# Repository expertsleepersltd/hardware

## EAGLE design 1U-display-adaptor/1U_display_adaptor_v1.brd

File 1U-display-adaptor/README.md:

1U Display Adaptor
=====

A mount for an OLED display to fit a Eurorack 1U row.

Copyright (c) 2022 Expert Sleepers Ltd

Please refer to [LICENSE.md](LICENSE.md) for licensing information.

Please note that Expert Sleepers® is a registered trade mark in the UK and the EU. Remove any branding before making a derivative work.

Board and schematic are in [EAGLE](https://en.wikipedia.org/wiki/EAGLE_(program)) format.

View as web page: https://expertsleepersltd.github.io/hardware/1U-display-adaptor/

The PCB can be purchased here: https://www.thonk.co.uk/shop/expert-sleepers-1u-display-pcb/

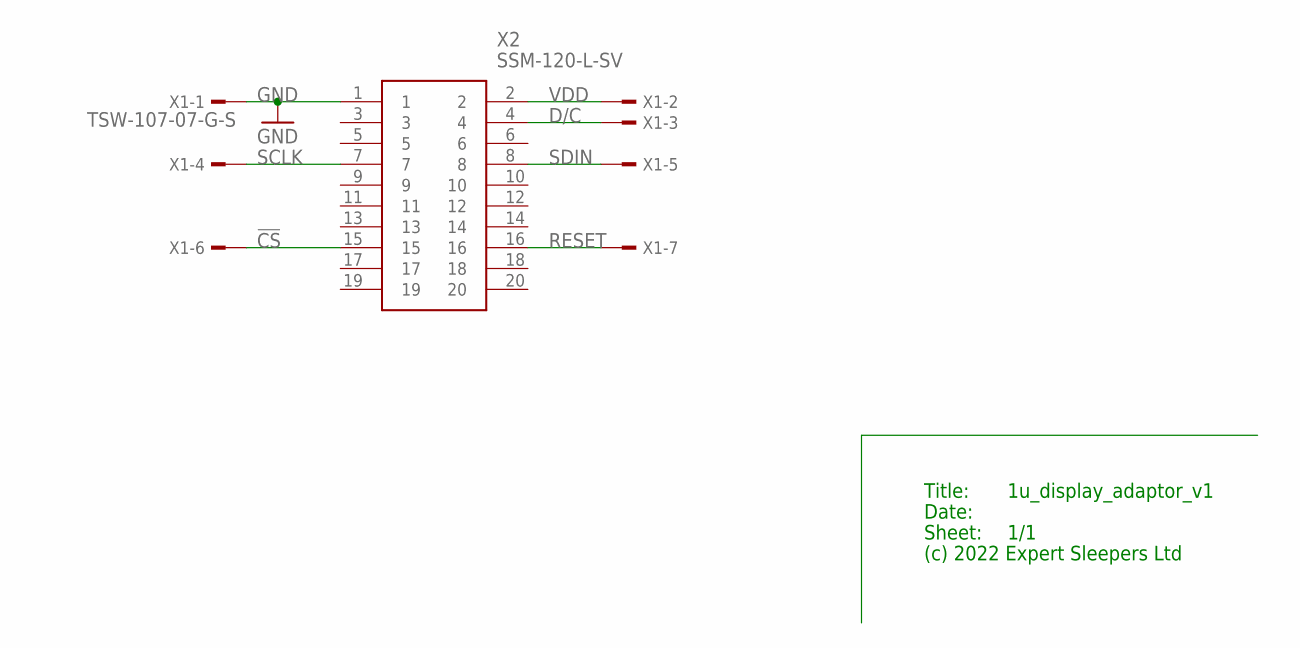
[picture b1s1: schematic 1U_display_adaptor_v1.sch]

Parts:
X1: TSW-107-07-G-S; TSW-107-XX-G-S
X2: SSM-120-L-SV; SSM120LSV

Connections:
!CS: X1.6, X2.15
D/C: X1.3, X2.4
GND: X1.1, X2.1
RESET: X1.7, X2.16
SCLK: X1.4, X2.7
SDIN: X1.5, X2.8
VDD: X1.2, X2.2

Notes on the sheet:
Title:
Date:
Sheet:
(c) 2022 Expert Sleepers Ltd

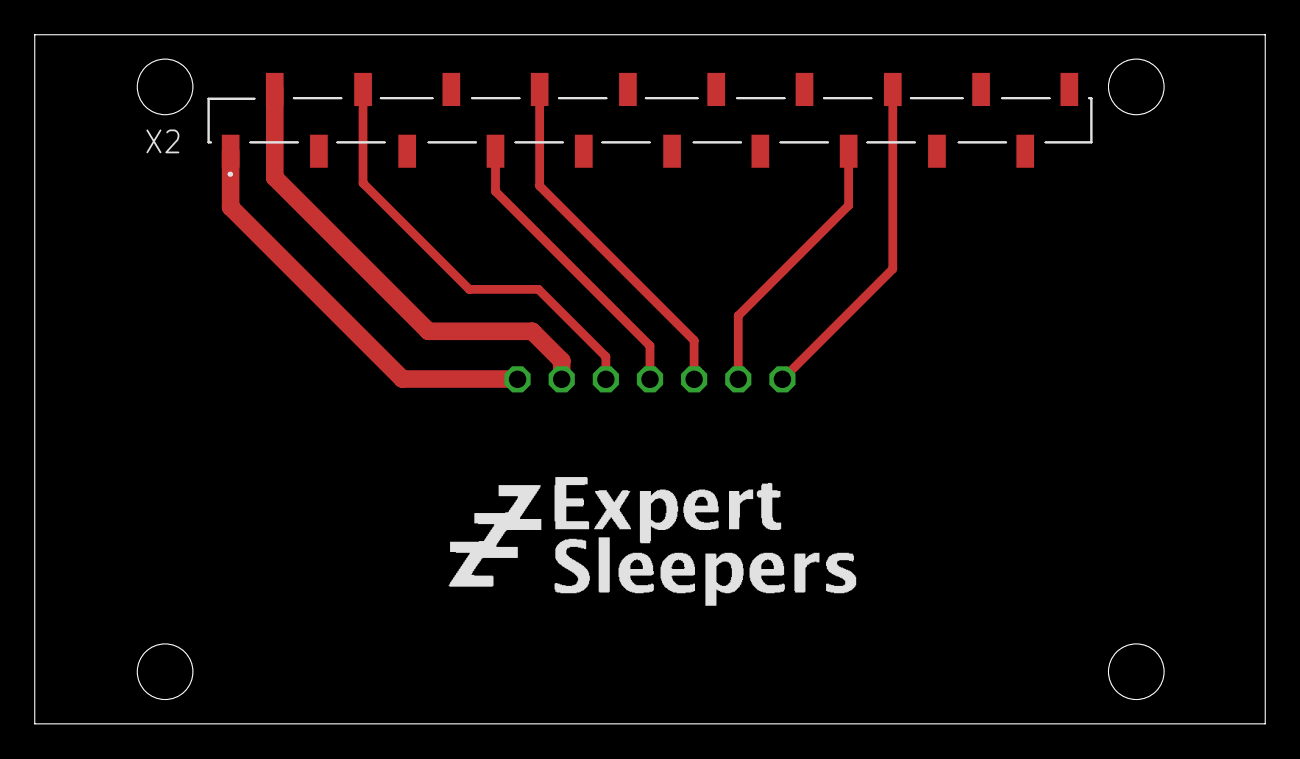
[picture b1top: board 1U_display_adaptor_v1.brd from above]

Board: 2 copper layers, 70.8 x 39.6 mm, 3 parts (1 on the bottom side), 7 nets.

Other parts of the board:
U$1: ES_ZZZ_TEXT_TPLACE_1IN_600DPI

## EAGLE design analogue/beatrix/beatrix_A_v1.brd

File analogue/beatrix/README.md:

Beatrix
=====

https://expert-sleepers.co.uk/beatrix.html

Copyright (c) 2021 Expert Sleepers Ltd

Please refer to [LICENSE.md](LICENSE.md) for licensing information.

Please note that Expert Sleepers® is a registered trade mark in the UK. Remove any branding before making a derivative work.

Front panel layout is [here](../../panels).

Board and schematic are in [EAGLE](https://en.wikipedia.org/wiki/EAGLE_(program)) format.

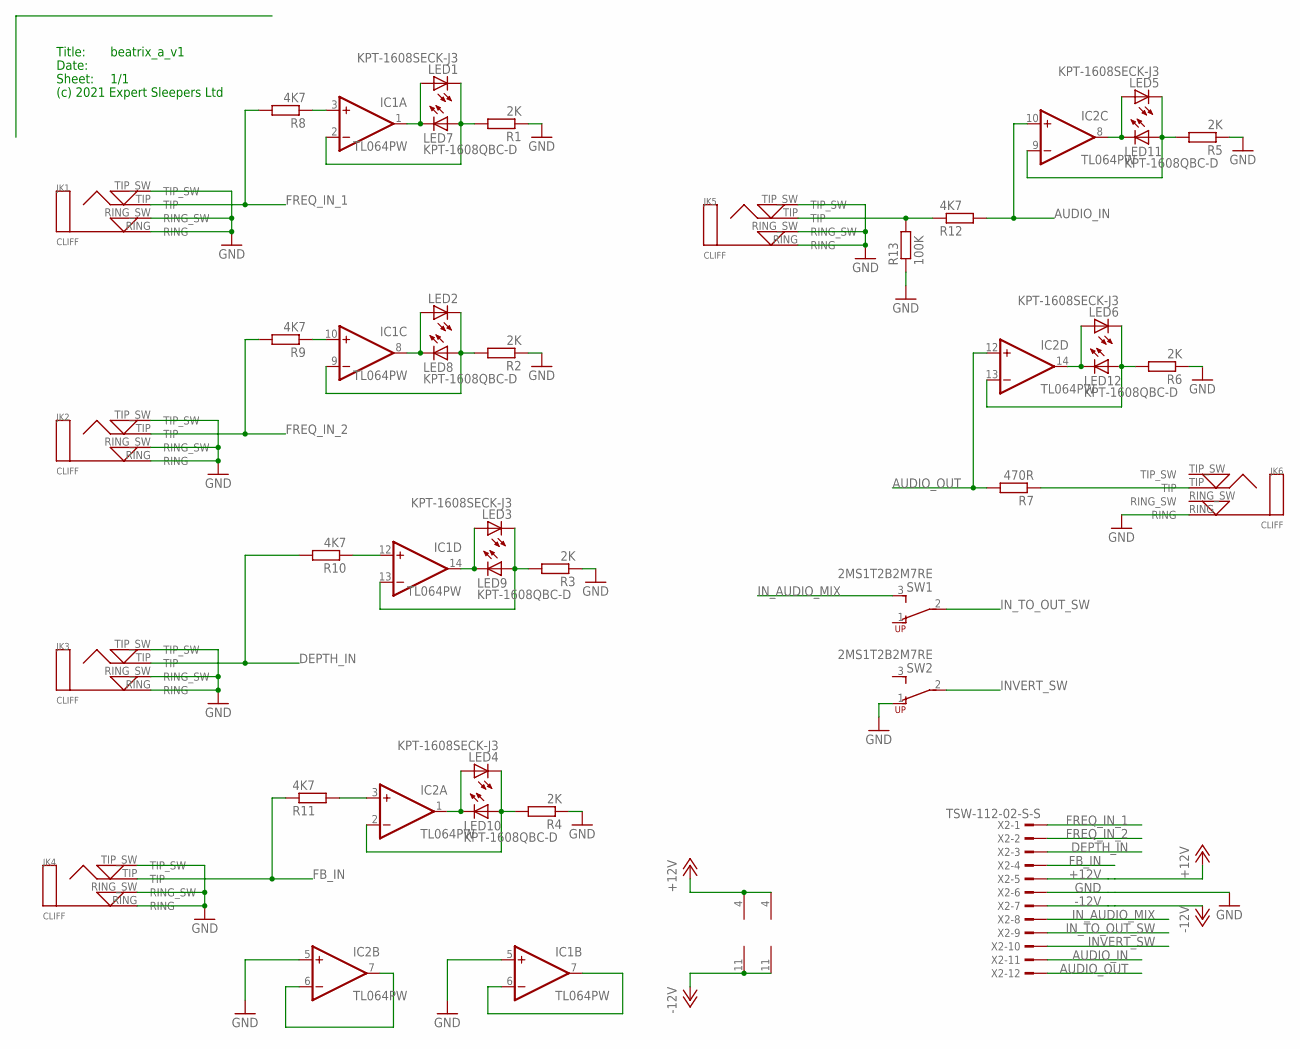
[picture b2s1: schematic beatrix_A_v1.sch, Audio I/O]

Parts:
IC1, IC2: TL064PW; PW_R-PDSO-G14
JK1, JK2, JK3, JK4, JK5, JK6: CLIFF; CLIFF3.5MMPCB
LED1, LED2, LED3, LED4, LED5, LED6: KPT-1608SECK-J3; CHIPLED_0603_LEFT
LED7, LED8, LED9, LED10, LED11, LED12: KPT-1608QBC-D; CHIPLED_0603_RIGHT
R1, R2, R3, R4, R5, R6: 2K; R1206
R7: 470R; R1206
R8, R9, R10, R11, R12: 4K7; R1206
R13: 100K; R0603
SW1, SW2: 2MS1T2B2M7RE
X2: TSW-112-02-S-S

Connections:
+12V: IC1.4 (V+), IC2.4 (V+), X2.5
-12V: IC1.11 (V-), IC2.11 (V-), X2.7
AUDIO_IN: IC2.10 (+IN), R12.2, X2.11
AUDIO_OUT: IC2.12 (+IN), R7.2, X2.12
DEPTH_IN: JK3.TIP, R10.2, X2.3
FB_IN: JK4.TIP, R11.1, X2.4
FREQ_IN_1: JK1.TIP, R8.2, X2.1
FREQ_IN_2: JK2.TIP, R9.2, X2.2
GND: IC1.5 (+IN), IC2.5 (+IN), JK1.RING, JK1.RING_SW, JK1.TIP_SW, JK2.RING, JK2.RING_SW, JK2.TIP_SW, JK3.RING, JK3.RING_SW, JK3.TIP_SW, JK4.RING, JK4.RING_SW, JK4.TIP_SW, JK5.RING, JK5.RING_SW, JK5.TIP_SW, JK6.RING, R1.1, R2.1, R3.1, R4.1, R5.1, R6.1, R13.1, SW2.1 (RU), X2.6
INVERT_SW: SW2.2 (PR), X2.10
IN_AUDIO_MIX: SW1.3 (RD), X2.8
IN_TO_OUT_SW: SW1.2 (PR), X2.9
unnamed: IC2.6 (-IN), IC2.7 (OUT)
unnamed: IC1.12 (+IN), R10.1
unnamed: IC1.14 (OUT), LED3.2 (A), LED9.2 (C)
unnamed: IC1.10 (+IN), R9.1
unnamed: IC1.13 (-IN), LED3.1 (C), LED9.1 (A), R3.2
unnamed: IC1.1 (OUT), LED1.2 (A), LED7.2 (C)
unnamed: IC1.2 (-IN), LED1.1 (C), LED7.1 (A), R1.2
unnamed: IC1.3 (+IN), R8.1
unnamed: IC1.8 (OUT), LED2.2 (A), LED8.2 (C)
unnamed: IC1.9 (-IN), LED2.1 (C), LED8.1 (A), R2.2
unnamed: IC1.6 (-IN), IC1.7 (OUT)
unnamed: IC2.3 (+IN), R11.2
unnamed: IC2.8 (OUT), LED5.2 (A), LED11.2 (C)
unnamed: IC2.9 (-IN), LED5.1 (C), LED11.1 (A), R5.2
unnamed: IC2.14 (OUT), LED6.2 (A), LED12.2 (C)
unnamed: IC2.13 (-IN), LED6.1 (C), LED12.1 (A), R6.2
unnamed: IC2.1 (OUT), LED4.2 (A), LED10.2 (C)
unnamed: IC2.2 (-IN), LED4.1 (C), LED10.1 (A), R4.2
unnamed: JK5.TIP, R12.1, R13.2
unnamed: JK6.TIP, R7.1

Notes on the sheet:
Title:
Date:
Sheet:
(c) 2021 Expert Sleepers Ltd

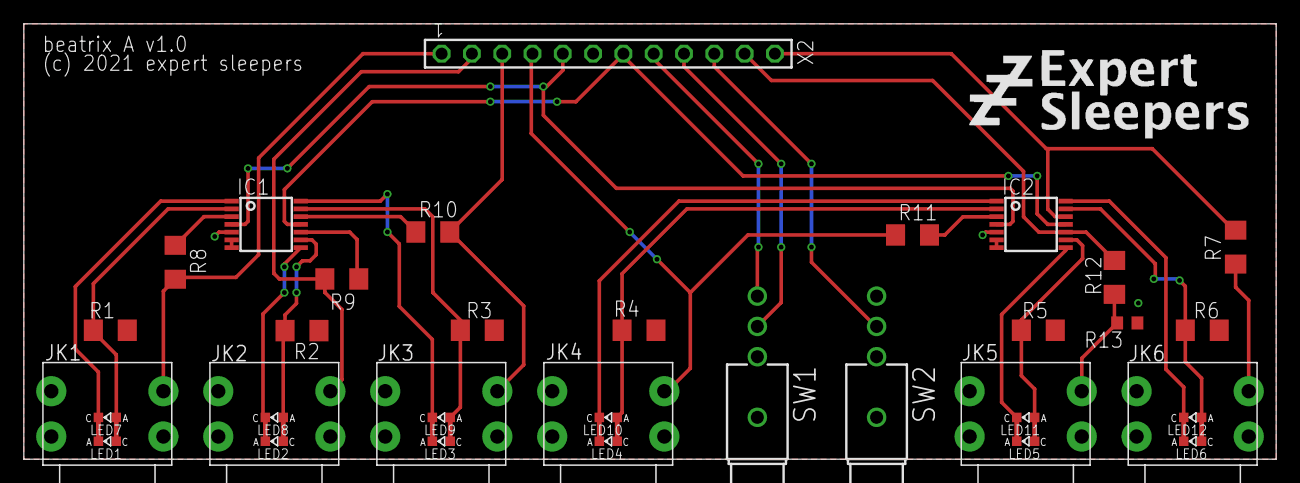
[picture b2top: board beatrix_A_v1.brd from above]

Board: 2 copper layers, 105.0 x 36.5 mm, 37 parts (0 on the bottom side), 32 nets.

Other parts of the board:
U$1: ES_ZZZ_TEXT_TPLACE_1IN_600DPI

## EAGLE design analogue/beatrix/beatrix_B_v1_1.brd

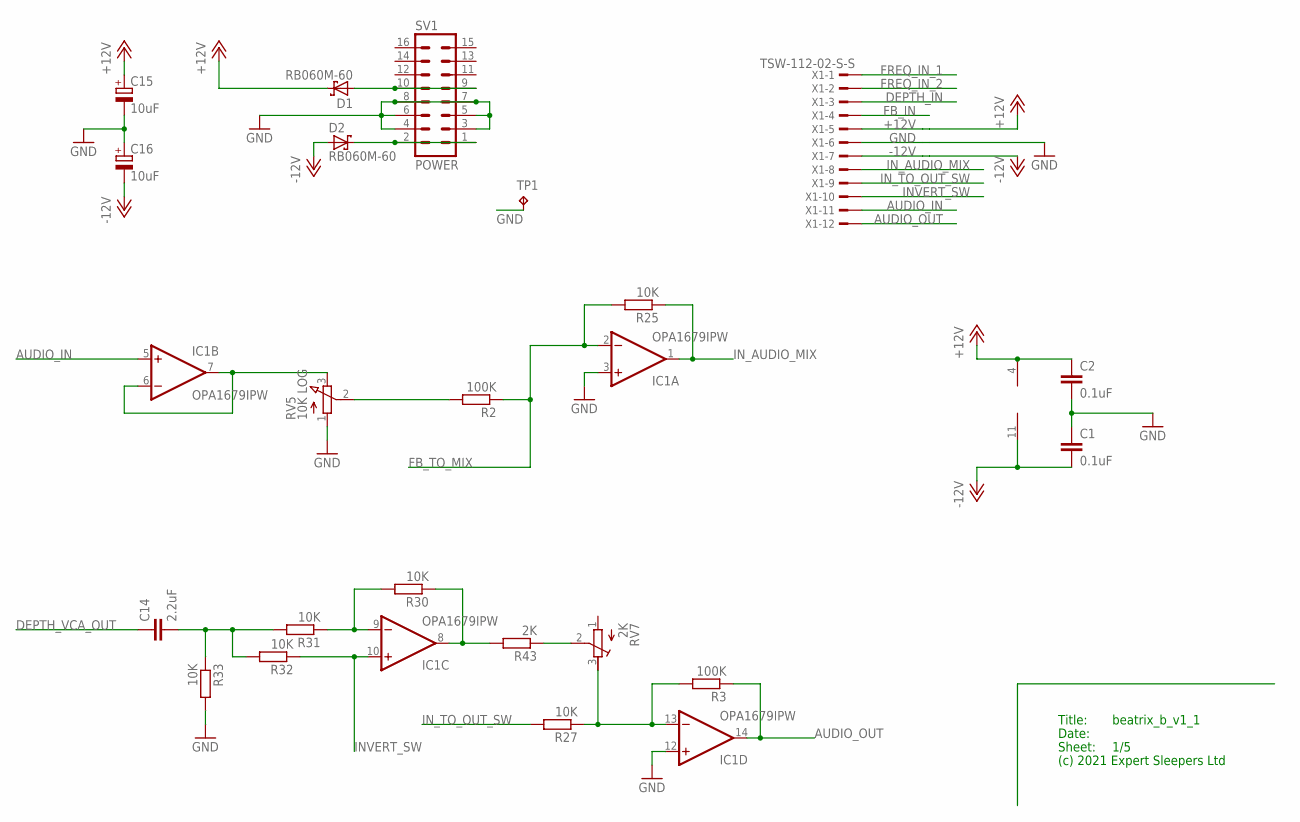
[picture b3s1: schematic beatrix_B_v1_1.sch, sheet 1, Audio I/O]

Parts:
C1, C2: 0.1uF; C0402
C14: 2.2uF; C0805
C15, C16: 10uF; UD-4X5,8_NICHICON
D1, D2: RB060M-60; SOD123FL
IC1: OPA1679IPW; PW_R-PDSO-G14
R2, R3: 100K; R0603
R25, R27, R30, R31, R32, R33: 10K; R0603
R43: 2K; R0603
RV5: 10K LOG; RD1610NOA0X
RV7: 2K; TC33X
SV1: POWER; ML16
TP1: RA2; P1-13
X1: TSW-112-02-S-S

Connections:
+12V: C2.1, C15.+, D1.C, IC1.4 (V+), X1.5; also elsewhere on the board
-12V: C1.2, C16.-, D2.A, IC1.11 (V-), X1.7; also elsewhere on the board
AUDIO_IN: IC1.5 (+IN), X1.11
AUDIO_OUT: IC1.14 (OUT), R3.1, X1.12
DEPTH_IN: X1.3; also elsewhere on the board
DEPTH_VCA_OUT: C14.1; also elsewhere on the board
FB_IN: X1.4; also elsewhere on the board
FB_TO_MIX: IC1.2 (-IN), R2.1, R25.2; also elsewhere on the board
FREQ_IN_1: X1.1; also elsewhere on the board
FREQ_IN_2: X1.2; also elsewhere on the board
GND: C1.1, C2.2, C15.-, C16.+, IC1.3 (+IN), IC1.12 (+IN), R33.2, RV5.1 (A), SV1.3, SV1.4, SV1.5, SV1.6, SV1.7, SV1.8, TP1.TP, X1.6; also elsewhere on the board
INVERT_SW: IC1.10 (+IN), R32.1, X1.10
IN_AUDIO_MIX: IC1.1 (OUT), R25.1, X1.8; also elsewhere on the board
IN_TO_OUT_SW: R27.2, X1.9
unnamed: D2.C, SV1.1, SV1.2
unnamed: IC1.8 (OUT), R30.1, R43.2
unnamed: IC1.13 (-IN), R3.2, R27.1, RV7.3 (E)
unnamed: IC1.6 (-IN), IC1.7 (OUT), RV5.3 (E)
unnamed: R2.2, RV5.2 (S)
unnamed: D1.A, SV1.9, SV1.10
unnamed: C14.2, R31.2, R32.2, R33.1
unnamed: R43.1, RV7.2 (S)
unnamed: IC1.9 (-IN), R30.2, R31.1

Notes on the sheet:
Title:
Date:
Sheet:
(c) 2021 Expert Sleepers Ltd

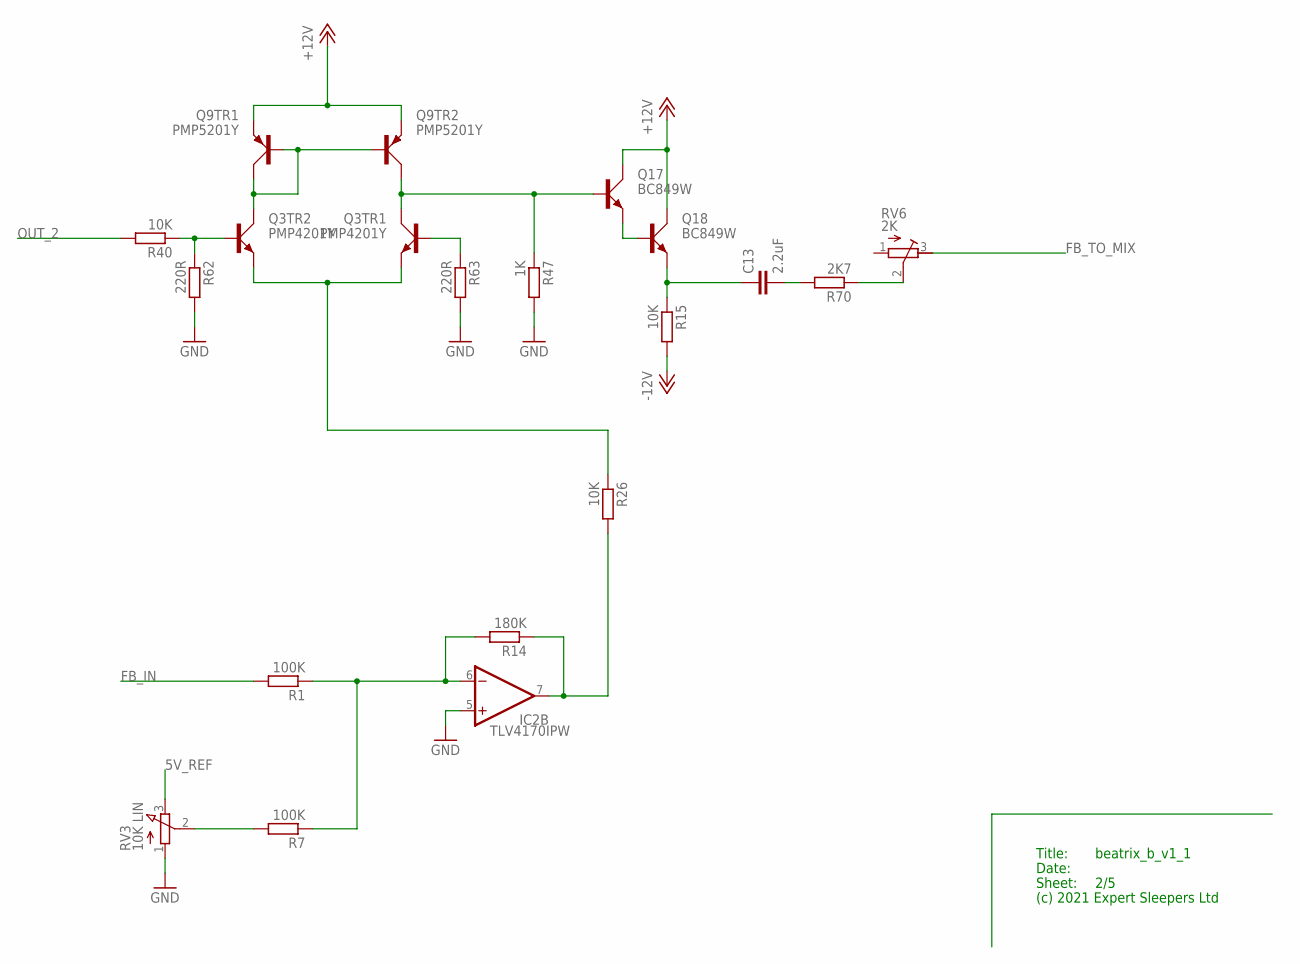
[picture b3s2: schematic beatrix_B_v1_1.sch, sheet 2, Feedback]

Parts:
C13: 2.2uF; C0805
IC2: TLV4170IPW; PW_R-PDSO-G14
Q3: PMP4201Y; SOT65P210X110-6N
Q9: PMP5201Y; SOT65P210X110-6N
Q17, Q18: BC849W; SOT323
R1, R7: 100K; R0603
R14: 180K; R0603
R15, R26, R40: 10K; R0603
R47: 1K; R0603
R62, R63: 220R; R0603
R70: 2K7; R0603
RV3: 10K LIN; RD1610NOA0X
RV6: 2K; TC33X

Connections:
5V_REF: RV3.3 (E); also elsewhere on the board
+12V: Q9.4 (E), Q9.5 (E), Q17.3 (C), Q18.3 (C); also elsewhere on the board
-12V: R15.2; also elsewhere on the board
FB_IN: R1.2; also elsewhere on the board
FB_TO_MIX: RV6.3 (E); also elsewhere on the board
GND: IC2.5 (+IN), R47.2, R62.2, R63.2, RV3.1 (A); also elsewhere on the board
unnamed: R70.1, RV6.2 (S)
unnamed: R7.2, RV3.2 (S)
unnamed: IC2.6 (-IN), R1.1, R7.1, R14.2
unnamed: IC2.7 (OUT), R14.1, R26.2
unnamed: C13.2, R70.2
unnamed: Q3.2 (B), R40.1, R62.1
unnamed: Q3.4 (E), Q3.5 (E), R26.1
unnamed: C13.1, Q18.2 (E), R15.1
unnamed: Q3.3 (C), Q9.1 (B), Q9.2 (B), Q9.6 (C)
unnamed: Q3.6 (C), Q9.3 (C), Q17.1 (B), R47.1
unnamed: Q3.1 (B), R63.1
unnamed: Q17.2 (E), Q18.1 (B)
OUT_2: R40.2; also elsewhere on the board

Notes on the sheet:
Title:
Date:
Sheet:
(c) 2021 Expert Sleepers Ltd

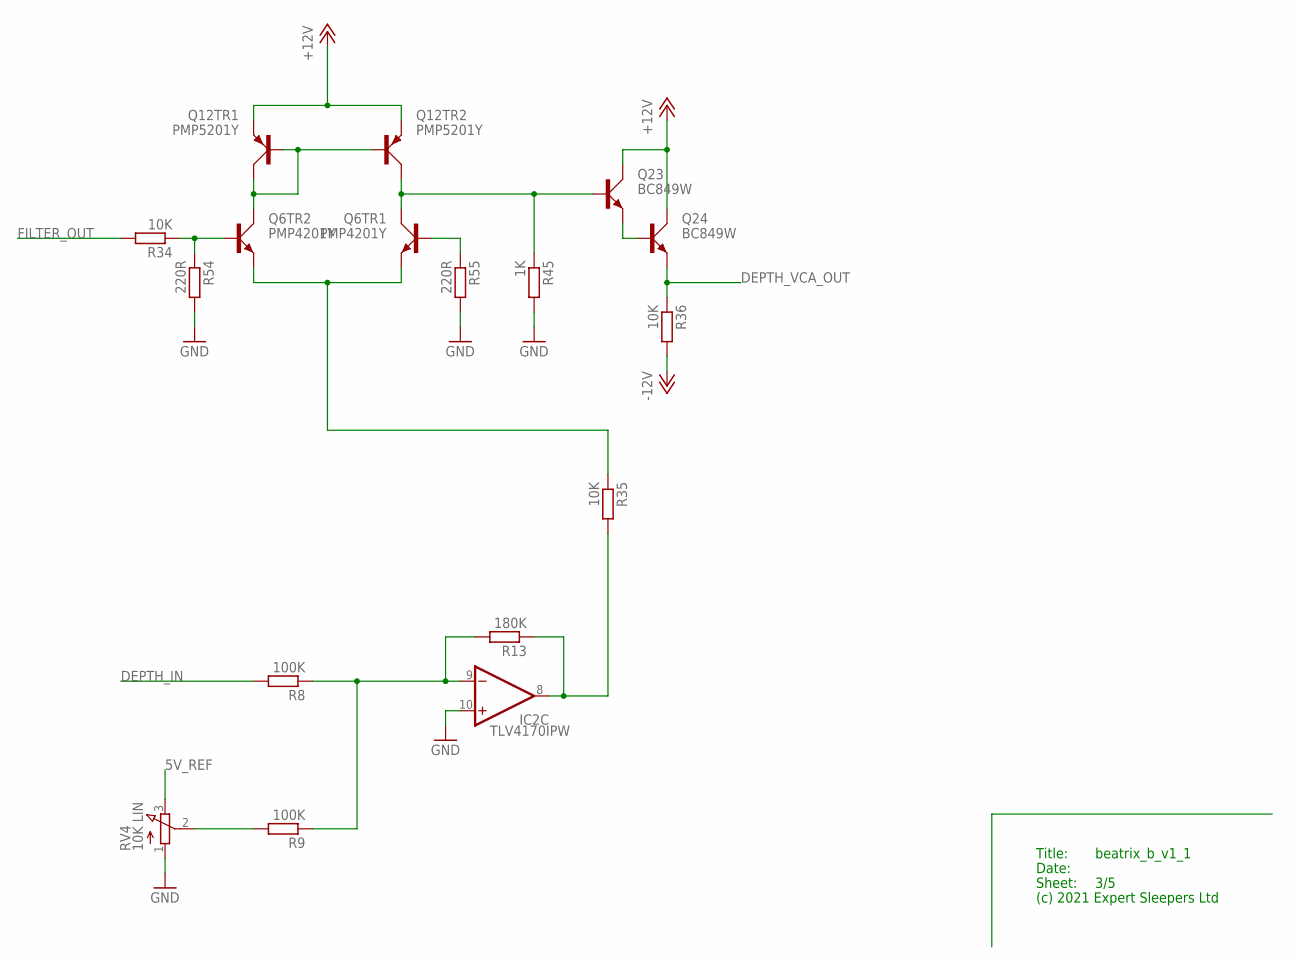
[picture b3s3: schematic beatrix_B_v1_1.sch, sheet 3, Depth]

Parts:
IC2: TLV4170IPW; PW_R-PDSO-G14
Q6: PMP4201Y; SOT65P210X110-6N
Q12: PMP5201Y; SOT65P210X110-6N
Q23, Q24: BC849W; SOT323
R8, R9: 100K; R0603
R13: 180K; R0603
R34, R35, R36: 10K; R0603
R45: 1K; R0603
R54, R55: 220R; R0603
RV4: 10K LIN; RD1610NOA0X

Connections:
5V_REF: RV4.3 (E); also elsewhere on the board
+12V: Q12.4 (E), Q12.5 (E), Q23.3 (C), Q24.3 (C); also elsewhere on the board
-12V: R36.2; also elsewhere on the board
DEPTH_IN: R8.2; also elsewhere on the board
DEPTH_VCA_OUT: Q24.2 (E), R36.1; also elsewhere on the board
FILTER_OUT: R34.2; also elsewhere on the board
GND: IC2.10 (+IN), R45.2, R54.2, R55.2, RV4.1 (A); also elsewhere on the board
unnamed: IC2.9 (-IN), R8.1, R9.1, R13.2
unnamed: IC2.8 (OUT), R13.1, R35.2
unnamed: Q6.2 (B), R34.1, R54.1
unnamed: Q6.4 (E), Q6.5 (E), R35.1
unnamed: Q6.3 (C), Q12.1 (B), Q12.2 (B), Q12.6 (C)
unnamed: Q6.6 (C), Q12.3 (C), Q23.1 (B), R45.1
unnamed: Q6.1 (B), R55.1
unnamed: Q23.2 (E), Q24.1 (B)
unnamed: R9.2, RV4.2 (S)

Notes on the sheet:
Title:
Date:
Sheet:
(c) 2021 Expert Sleepers Ltd

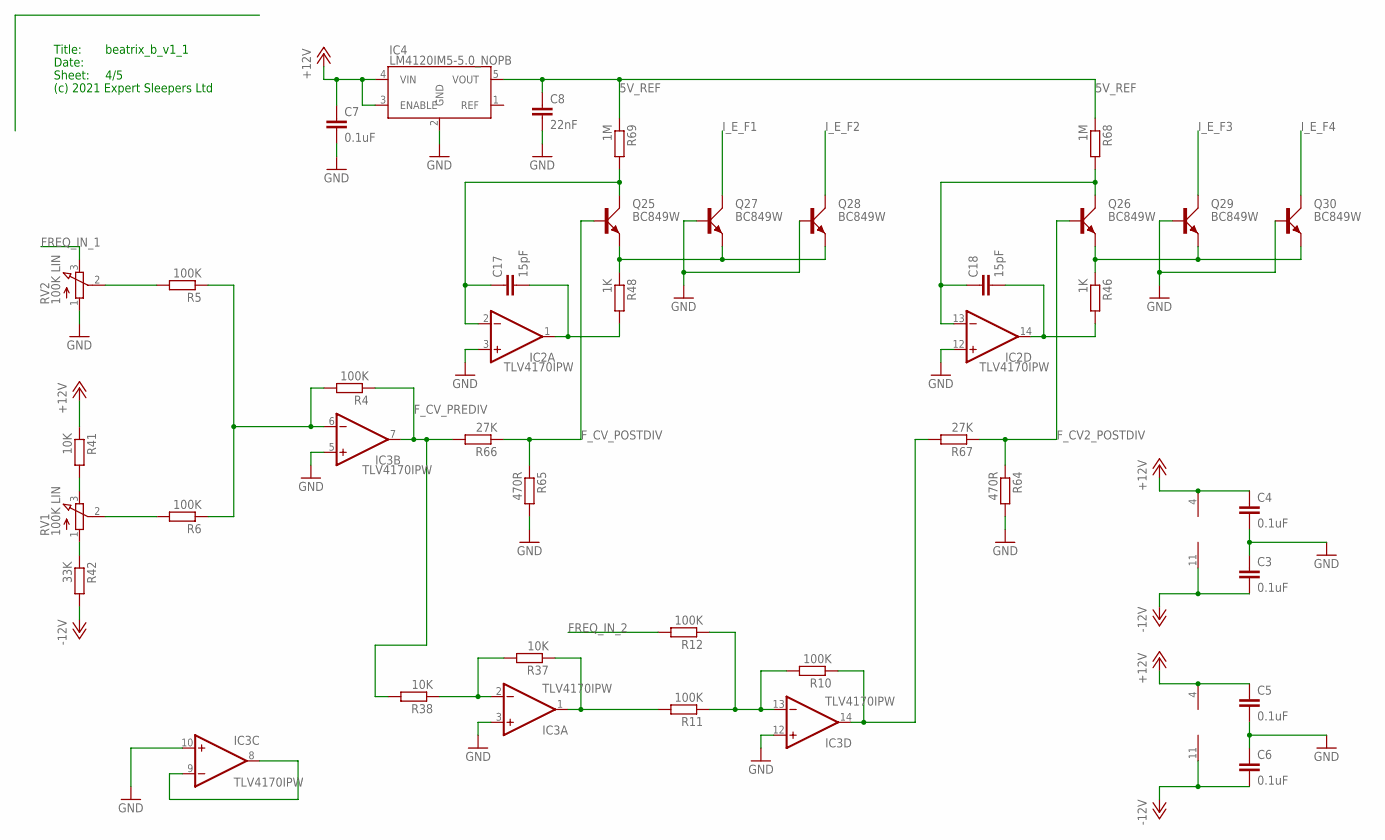
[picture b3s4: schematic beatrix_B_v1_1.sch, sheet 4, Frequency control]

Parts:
C3, C4, C5, C6, C7: 0.1uF; C0402
C8: 22nF; C0402
C17, C18: 15pF; C0402
IC2, IC3: TLV4170IPW; PW_R-PDSO-G14
IC4: LM4120IM5-5.0_NOPB; SOT95P280X145-5N
Q25, Q26, Q27, Q28, Q29, Q30: BC849W; SOT323
R4, R5, R6, R10, R11, R12: 100K; R0603
R37, R38, R41: 10K; R0603
R42: 33K; R0603
R46, R48: 1K; R0603
R64, R65: 470R; R0603
R66, R67: 27K; R0603
R68, R69: 1M; R0603
RV1, RV2: 100K LIN; RD1610NOA0X

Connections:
5V_REF: C8.1, IC4.5 (VOUT), R68.1, R69.1; also elsewhere on the board
+12V: C4.1, C5.1, C7.1, IC2.4 (V+), IC3.4 (V+), IC4.3 (ENABLE), IC4.4 (VIN), R41.1; also elsewhere on the board
-12V: C3.2, C6.2, IC2.11 (V-), IC3.11 (V-), R42.2; also elsewhere on the board
FREQ_IN_1: RV2.3 (E); also elsewhere on the board
FREQ_IN_2: R12.2; also elsewhere on the board
F_CV2_POSTDIV: Q26.1 (B), R64.1, R67.1
F_CV_POSTDIV: Q25.1 (B), R65.1, R66.1
F_CV_PREDIV: IC3.7 (OUT), R4.1, R38.2, R66.2
GND: C3.1, C4.2, C5.2, C6.1, C7.2, C8.2, IC2.3 (+IN), IC2.12 (+IN), IC3.3 (+IN), IC3.5 (+IN), IC3.10 (+IN), IC3.12 (+IN), IC4.2 (GND), Q27.1 (B), Q28.1 (B), Q29.1 (B), Q30.1 (B), R64.2, R65.2, RV2.1 (A); also elsewhere on the board
I_E_F1: Q27.3 (C); also elsewhere on the board
I_E_F2: Q28.3 (C); also elsewhere on the board
I_E_F3: Q29.3 (C); also elsewhere on the board
I_E_F4: Q30.3 (C); also elsewhere on the board
unnamed: R42.1, RV1.1 (A)
unnamed: IC3.6 (-IN), R4.2, R5.1, R6.1
unnamed: IC3.8 (OUT), IC3.9 (-IN)
unnamed: R5.2, RV2.2 (S)
unnamed: R6.2, RV1.2 (S)
unnamed: R41.2, RV1.3 (E)
unnamed: Q25.2 (E), Q27.2 (E), Q28.2 (E), R48.1
unnamed: C17.1, IC2.2 (-IN), Q25.3 (C), R69.2
unnamed: C17.2, IC2.1 (OUT), R48.2
unnamed: Q26.2 (E), Q29.2 (E), Q30.2 (E), R46.1
unnamed: C18.1, IC2.13 (-IN), Q26.3 (C), R68.2
unnamed: C18.2, IC2.14 (OUT), R46.2
unnamed: IC3.2 (-IN), R37.2, R38.1
unnamed: IC3.1 (OUT), R11.2, R37.1
unnamed: IC3.13 (-IN), R10.2, R11.1, R12.1
unnamed: IC3.14 (OUT), R10.1, R67.2

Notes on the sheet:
Title:
Date:
Sheet:
(c) 2021 Expert Sleepers Ltd

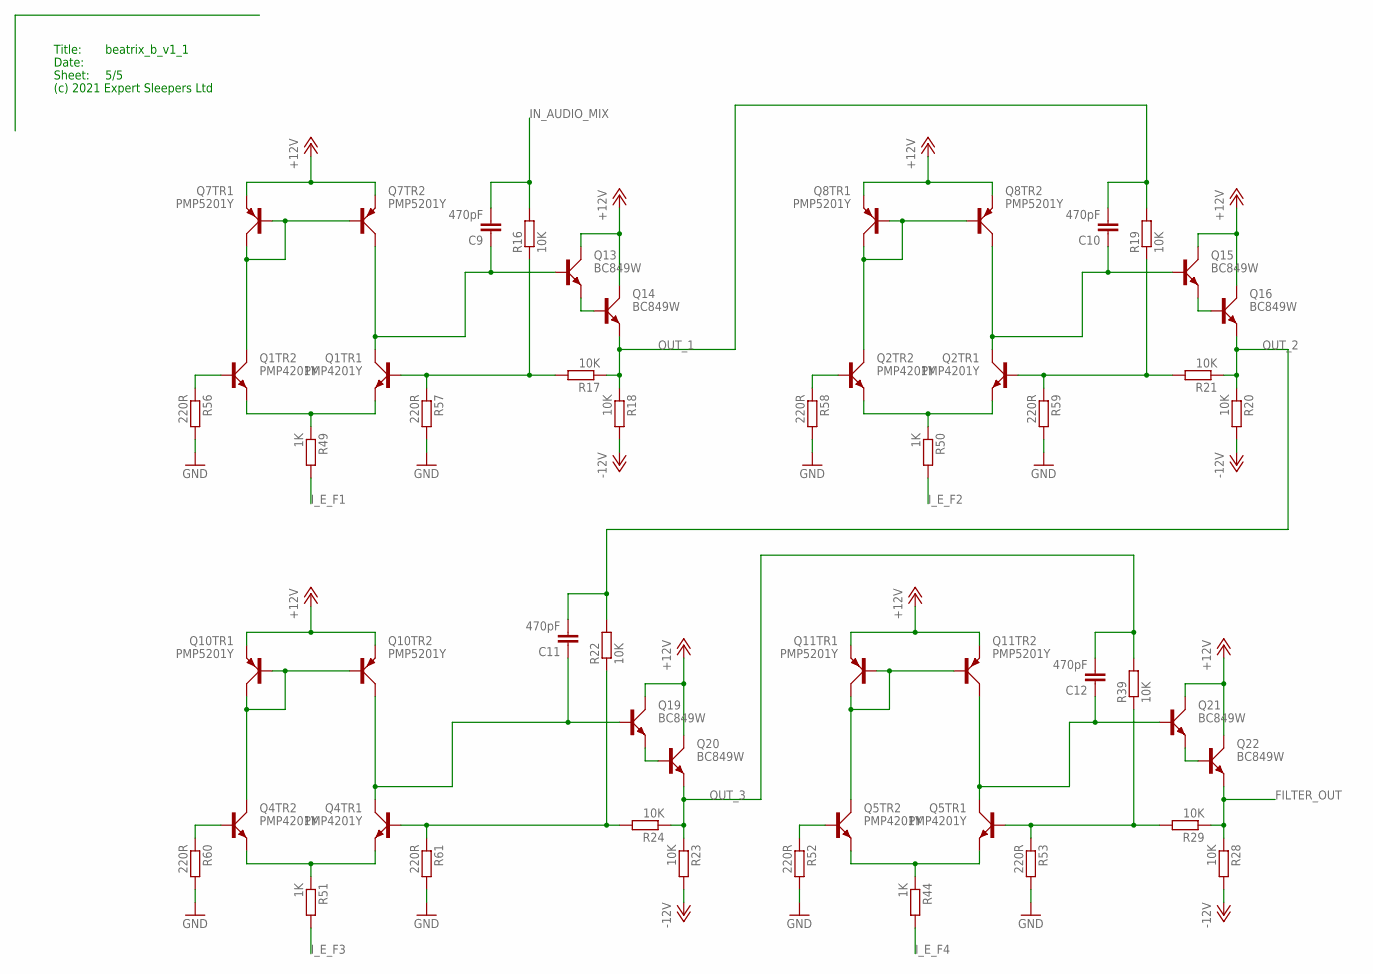
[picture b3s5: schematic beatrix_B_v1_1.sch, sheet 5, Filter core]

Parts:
C9, C10, C11, C12: 470pF; C0603
Q1, Q2, Q4, Q5: PMP4201Y; SOT65P210X110-6N
Q7, Q8, Q10, Q11: PMP5201Y; SOT65P210X110-6N
Q13, Q14, Q15, Q16, Q19, Q20, Q21, Q22: BC849W; SOT323
R16, R17, R18, R19, R20, R21, R22, R23, R24, R28, R29, R39: 10K; R0603
R44, R49, R50, R51: 1K; R0603
R52, R53, R56, R57, R58, R59, R60, R61: 220R; R0603

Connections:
+12V: Q7.4 (E), Q7.5 (E), Q8.4 (E), Q8.5 (E), Q10.4 (E), Q10.5 (E), Q11.4 (E), Q11.5 (E), Q13.3 (C), Q14.3 (C), Q15.3 (C), Q16.3 (C), Q19.3 (C), Q20.3 (C), Q21.3 (C), Q22.3 (C); also elsewhere on the board
-12V: R18.2, R20.2, R23.2, R28.2; also elsewhere on the board
FILTER_OUT: Q22.2 (E), R28.1, R29.1; also elsewhere on the board
GND: R52.2, R53.2, R56.2, R57.2, R58.2, R59.2, R60.2, R61.2; also elsewhere on the board
IN_AUDIO_MIX: C9.2, R16.2; also elsewhere on the board
I_E_F1: R49.2; also elsewhere on the board
I_E_F2: R50.2; also elsewhere on the board
I_E_F3: R51.2; also elsewhere on the board
I_E_F4: R44.2; also elsewhere on the board
unnamed: Q1.2 (B), R56.1
unnamed: Q5.2 (B), R52.1
unnamed: Q1.4 (E), Q1.5 (E), R49.1
unnamed: Q5.4 (E), Q5.5 (E), R44.1
unnamed: C12.1, Q5.6 (C), Q11.3 (C), Q21.1 (B)
unnamed: Q5.1 (B), R29.2, R39.1, R53.1
unnamed: Q21.2 (E), Q22.1 (B)
unnamed: Q5.3 (C), Q11.1 (B), Q11.2 (B), Q11.6 (C)
unnamed: C9.1, Q1.6 (C), Q7.3 (C), Q13.1 (B)
unnamed: Q1.3 (C), Q7.1 (B), Q7.2 (B), Q7.6 (C)
unnamed: Q1.1 (B), R16.1, R17.2, R57.1
unnamed: Q13.2 (E), Q14.1 (B)
unnamed: Q2.2 (B), R58.1
unnamed: Q2.4 (E), Q2.5 (E), R50.1
unnamed: C10.1, Q2.6 (C), Q8.3 (C), Q15.1 (B)
unnamed: Q2.1 (B), R19.1, R21.2, R59.1
unnamed: Q15.2 (E), Q16.1 (B)
unnamed: Q2.3 (C), Q8.1 (B), Q8.2 (B), Q8.6 (C)
unnamed: Q4.2 (B), R60.1
unnamed: Q4.4 (E), Q4.5 (E), R51.1
unnamed: C11.1, Q4.6 (C), Q10.3 (C), Q19.1 (B)
unnamed: Q4.1 (B), R22.1, R24.2, R61.1
unnamed: Q19.2 (E), Q20.1 (B)
unnamed: Q4.3 (C), Q10.1 (B), Q10.2 (B), Q10.6 (C)
OUT_1: C10.2, Q14.2 (E), R17.1, R18.1, R19.2
OUT_2: C11.2, Q16.2 (E), R20.1, R21.1, R22.2; also elsewhere on the board
OUT_3: C12.2, Q20.2 (E), R23.1, R24.1, R39.2

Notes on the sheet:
Title:
Date:
Sheet:
(c) 2021 Expert Sleepers Ltd

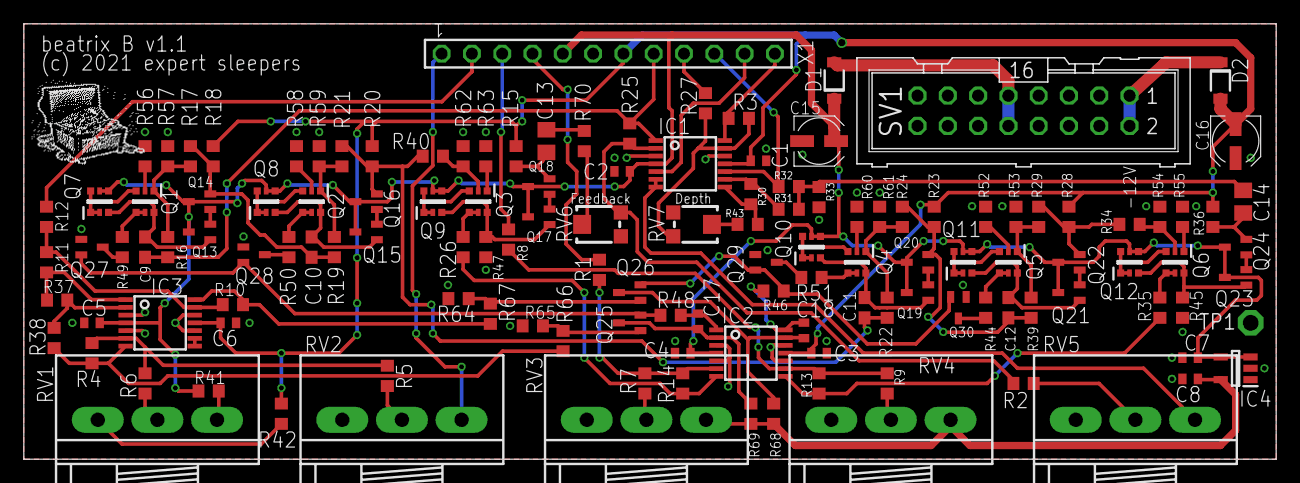
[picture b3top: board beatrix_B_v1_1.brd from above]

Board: 2 copper layers, 105.0 x 36.5 mm, 135 parts (0 on the bottom side), 96 nets.

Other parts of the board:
U$2: TREASURE_10MM_300DPI

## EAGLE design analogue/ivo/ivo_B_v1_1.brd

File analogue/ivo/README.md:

Ivo
=====

https://expert-sleepers.co.uk/ivo.html

Copyright (c) 2021 Expert Sleepers Ltd

Please refer to [LICENSE.md](LICENSE.md) for licensing information.

Please note that Expert Sleepers® is a registered trade mark in the UK. Remove any branding before making a derivative work.

Front panel layout is [here](../../panels).

Board and schematic are in [EAGLE](https://en.wikipedia.org/wiki/EAGLE_(program)) format.

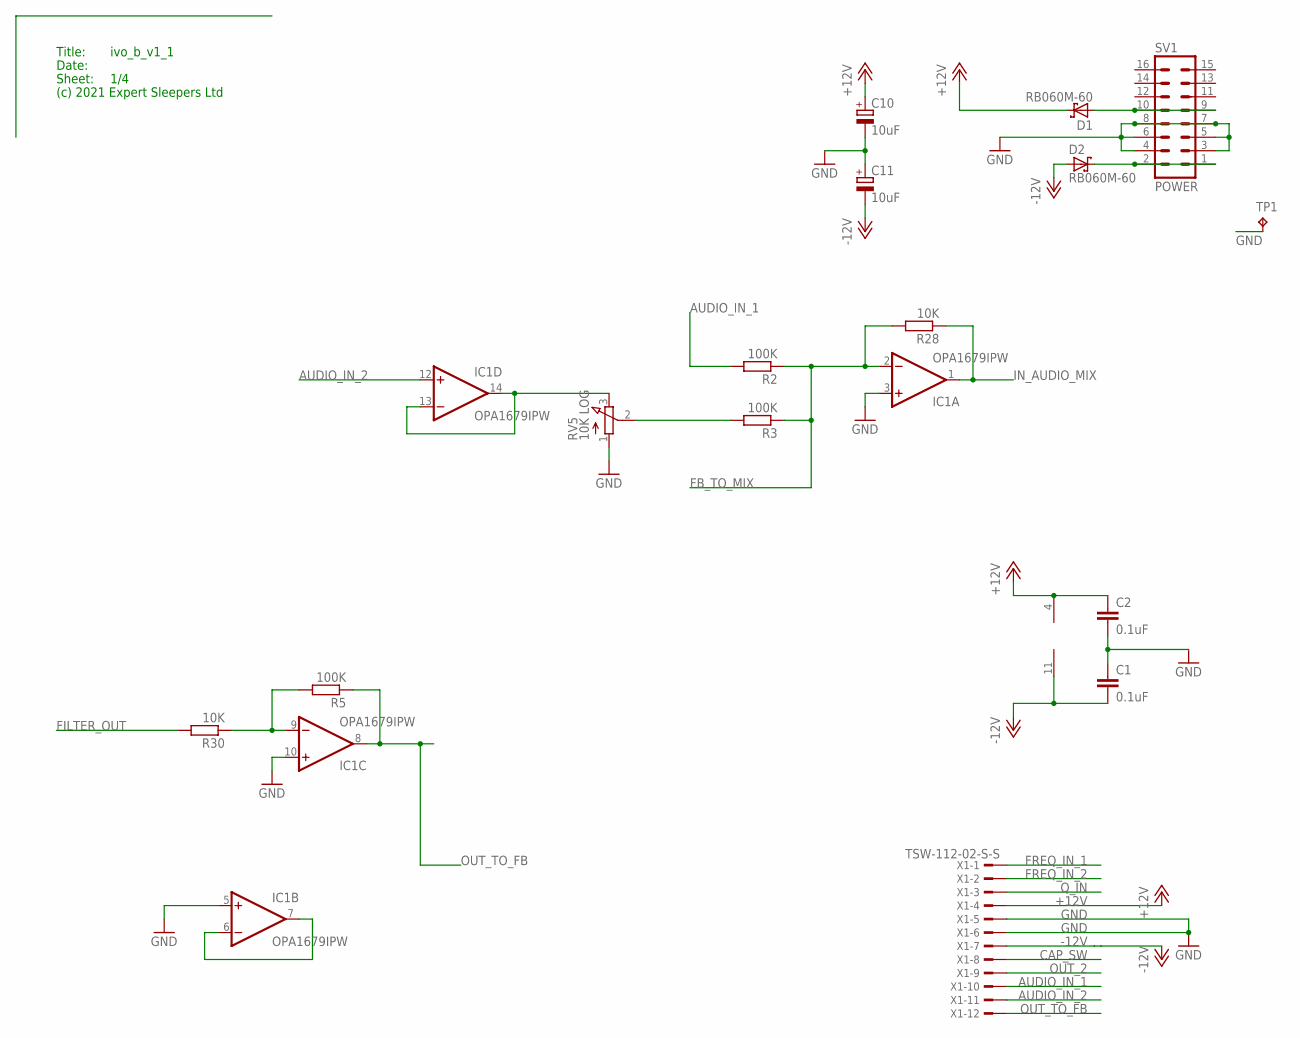
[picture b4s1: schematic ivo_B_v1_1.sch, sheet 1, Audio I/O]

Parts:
C1, C2: 0.1uF; C0402
C10, C11: 10uF; UD-4X5,8_NICHICON
D1, D2: RB060M-60; SOD123FL
IC1: OPA1679IPW; PW_R-PDSO-G14
R2, R3, R5: 100K; R0603
R28, R30: 10K; R0603
RV5: 10K LOG; RD1610NOA0X
SV1: POWER; ML16
TP1: RA2; P1-13
X1: TSW-112-02-S-S

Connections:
+12V: C2.1, C10.+, D1.C, IC1.4 (V+), X1.4; also elsewhere on the board
-12V: C1.2, C11.-, D2.A, IC1.11 (V-), X1.7; also elsewhere on the board
AUDIO_IN_1: R2.2, X1.10
AUDIO_IN_2: IC1.12 (+IN), X1.11
CAP_SW: X1.8; also elsewhere on the board
FB_TO_MIX: IC1.2 (-IN), R2.1, R3.1, R28.2; also elsewhere on the board
FILTER_OUT: R30.2; also elsewhere on the board
FREQ_IN_1: X1.1; also elsewhere on the board
FREQ_IN_2: X1.2; also elsewhere on the board
GND: C1.1, C2.2, C10.-, C11.+, IC1.3 (+IN), IC1.5 (+IN), IC1.10 (+IN), RV5.1 (A), SV1.3, SV1.4, SV1.5, SV1.6, SV1.7, SV1.8, TP1.TP, X1.5, X1.6; also elsewhere on the board
IN_AUDIO_MIX: IC1.1 (OUT), R28.1; also elsewhere on the board
unnamed: D2.C, SV1.1, SV1.2
unnamed: IC1.6 (-IN), IC1.7 (OUT)
unnamed: IC1.9 (-IN), R5.2, R30.1
unnamed: IC1.13 (-IN), IC1.14 (OUT), RV5.3 (E)
unnamed: R3.2, RV5.2 (S)
unnamed: D1.A, SV1.9, SV1.10
OUT_2: X1.9; also elsewhere on the board
OUT_TO_FB: IC1.8 (OUT), R5.1, X1.12; also elsewhere on the board
Q_IN: X1.3; also elsewhere on the board

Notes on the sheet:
Title:
Date:
Sheet:
(c) 2021 Expert Sleepers Ltd

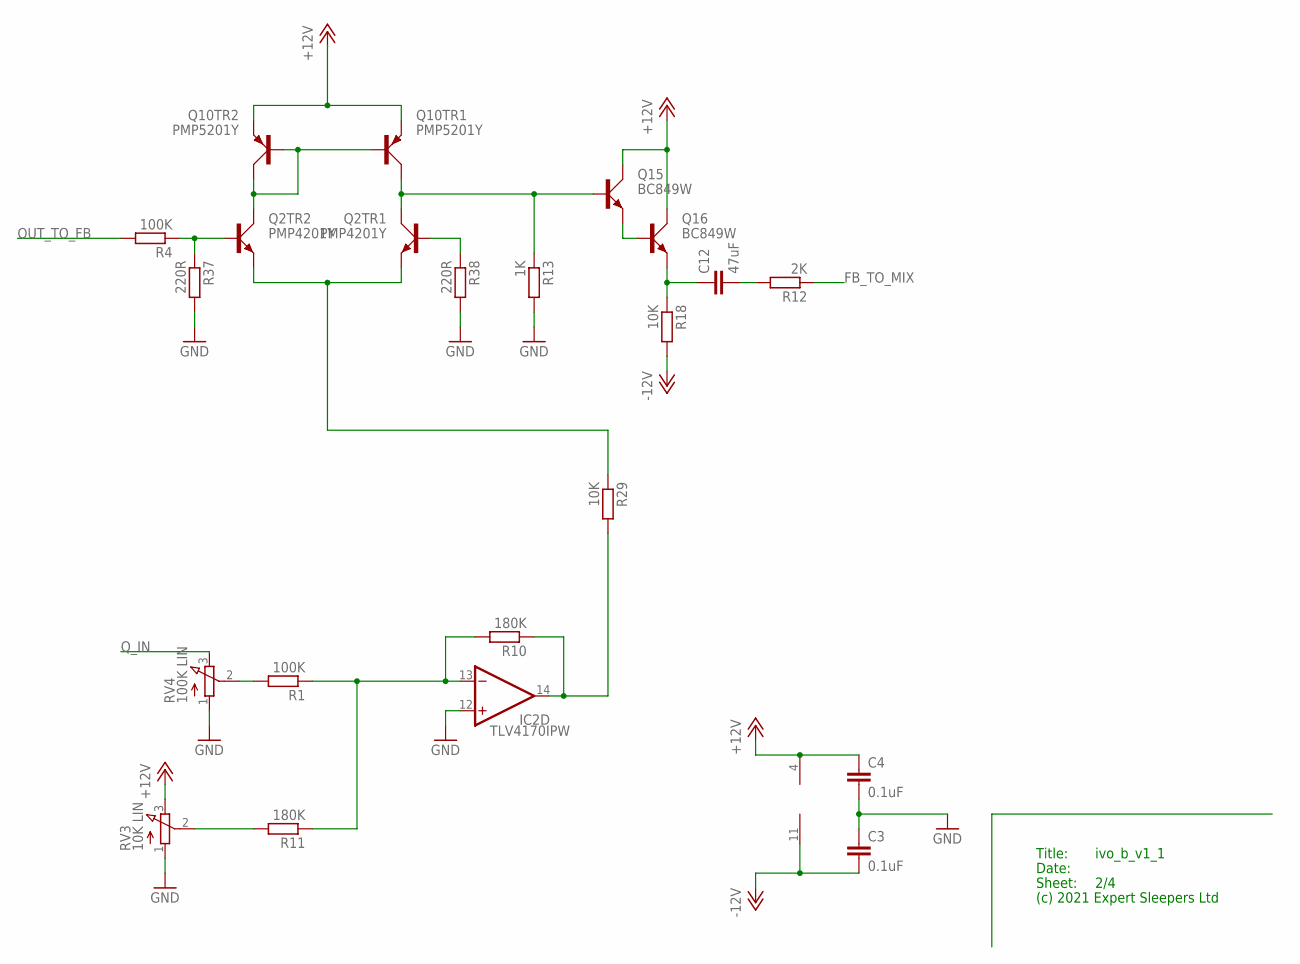
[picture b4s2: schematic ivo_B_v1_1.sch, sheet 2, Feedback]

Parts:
C3, C4: 0.1uF; C0402
C12: 47uF; C1206
IC2: TLV4170IPW; PW_R-PDSO-G14
Q2: PMP4201Y; SOT65P210X110-6N
Q10: PMP5201Y; SOT65P210X110-6N
Q15, Q16: BC849W; SOT323
R1, R4: 100K; R0603
R10, R11: 180K; R0603
R12: 2K; R0603
R13: 1K; R0603
R18, R29: 10K; R0603
R37, R38: 220R; R0603
RV3: 10K LIN; RD1610NOA0X
RV4: 100K LIN; RD1610NOA0X

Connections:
+12V: C4.1, IC2.4 (V+), Q10.4 (E), Q10.5 (E), Q15.3 (C), Q16.3 (C), RV3.3 (E); also elsewhere on the board
-12V: C3.2, IC2.11 (V-), R18.2; also elsewhere on the board
FB_TO_MIX: R12.1; also elsewhere on the board
GND: C3.1, C4.2, IC2.12 (+IN), R13.2, R37.2, R38.2, RV3.1 (A), RV4.1 (A); also elsewhere on the board
unnamed: R1.2, RV4.2 (S)
unnamed: R11.2, RV3.2 (S)
unnamed: IC2.13 (-IN), R1.1, R10.2, R11.1
unnamed: IC2.14 (OUT), R10.1, R29.2
unnamed: C12.2, R12.2
unnamed: Q2.2 (B), R4.1, R37.1
unnamed: Q2.4 (E), Q2.5 (E), R29.1
unnamed: C12.1, Q16.2 (E), R18.1
unnamed: Q2.3 (C), Q10.1 (B), Q10.2 (B), Q10.3 (C)
unnamed: Q2.6 (C), Q10.6 (C), Q15.1 (B), R13.1
unnamed: Q2.1 (B), R38.1
unnamed: Q15.2 (E), Q16.1 (B)
OUT_TO_FB: R4.2; also elsewhere on the board
Q_IN: RV4.3 (E); also elsewhere on the board

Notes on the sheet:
Title:
Date:
Sheet:
(c) 2021 Expert Sleepers Ltd
